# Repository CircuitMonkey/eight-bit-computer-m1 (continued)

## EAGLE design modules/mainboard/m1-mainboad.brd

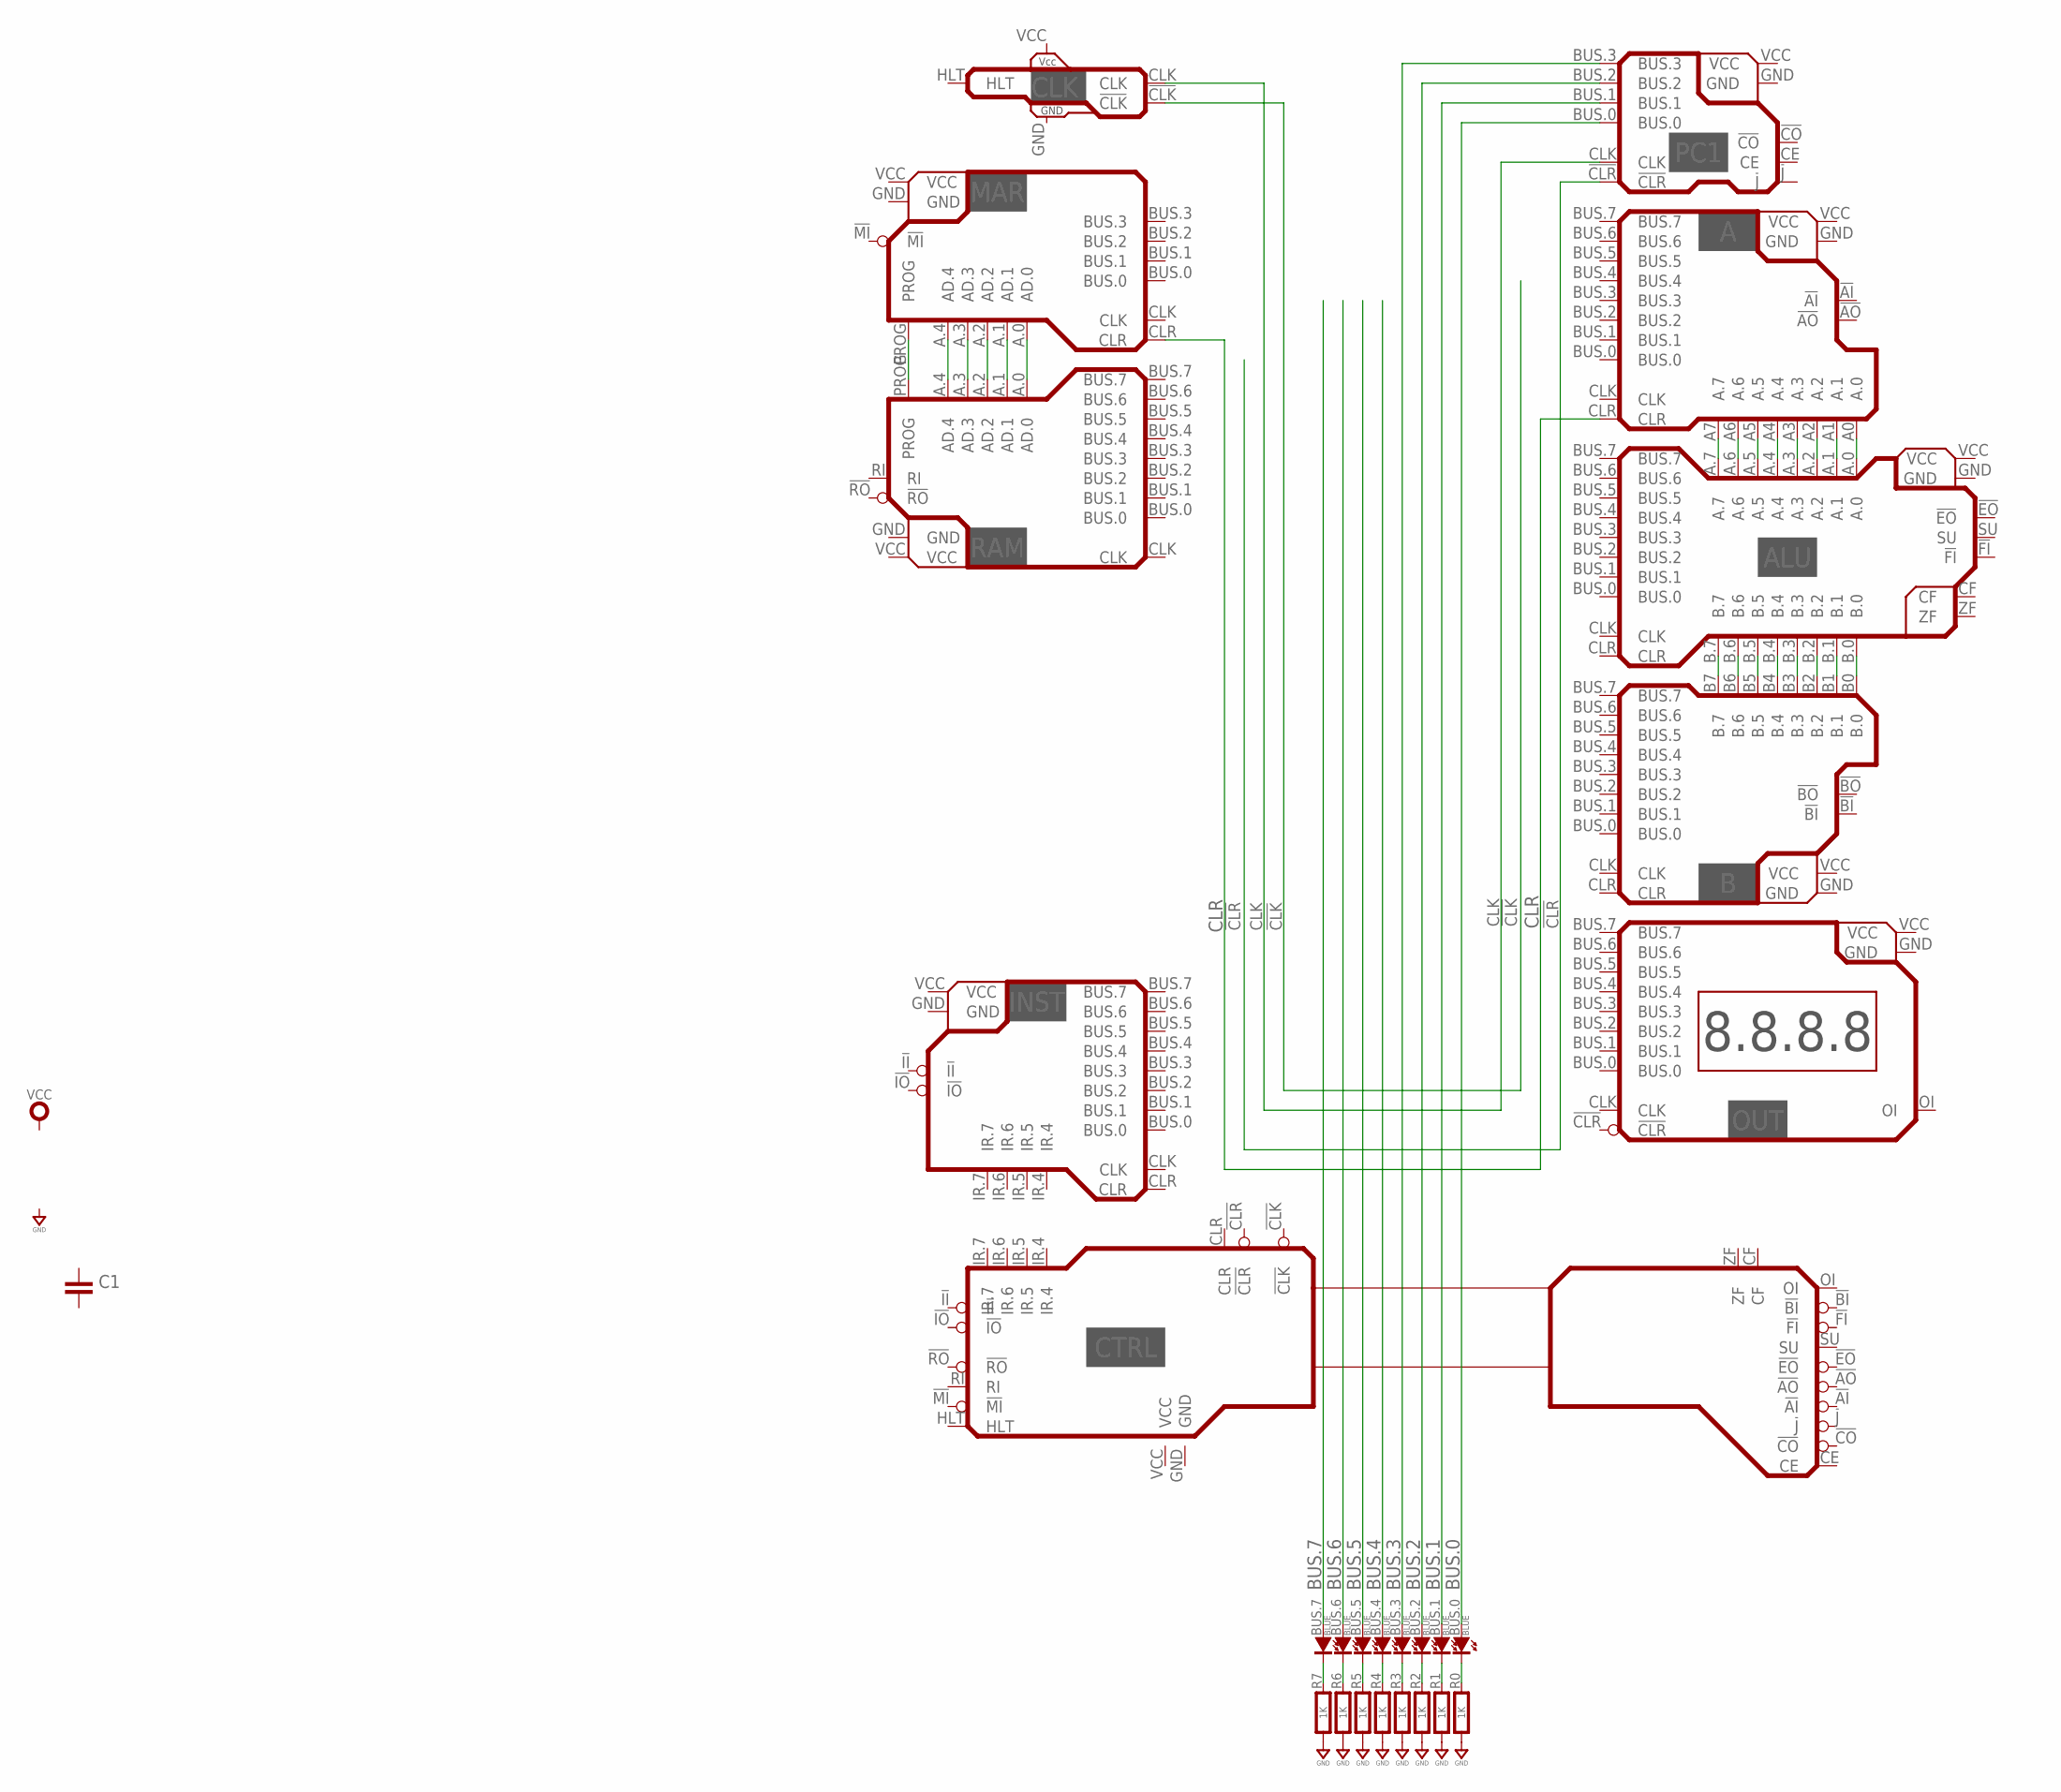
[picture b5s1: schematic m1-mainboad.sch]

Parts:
A: M1-REG-A-REV-A; M1-REG-A
ALU: M1-ALU-REV-A; M1-ALU
B: M1-REG-B-REV-A; M1-REG-B
BUS.0, BUS.1, BUS.2, BUS.3, BUS.4, BUS.5, BUS.6, BUS.7: BLUE; SMD_0603
C1: CAPACITOR0603; 0603-CAP
CLK: M1-CLOCKREV-A; M1-CLOCK
CTRL: M1-CONTROL-REV-A; M1-CONTROL
INST: M1-REG-INSTR-REV-A; M1-REG-I
MAR: M1-MAR-REV-A; M1-MAR
OUT: M1-REG-OUTPUT-REV-A; M1-REG-OUTPUT
PC1: M1-PROG-COUNTERREV-A; M1-PROGRAM-COUNTER
R0, R1, R2, R3, R4, R5, R6, R7: 1K; 0603-RES
RAM: M1-RAM-REV-A; M1-RAM

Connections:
!CLK: CLK.!CLK
!CLR: PC1.!CLR
BUS.0: BUS.0.A, PC1.BUS.0
BUS.1: BUS.1.A, PC1.BUS.1
BUS.2: BUS.2.A, PC1.BUS.2
BUS.3: BUS.3.A, PC1.BUS.3
BUS.4: BUS.4.A
BUS.5: BUS.5.A
BUS.6: BUS.6.A
BUS.7: BUS.7.A
CLK: CLK.CLK, PC1.CLK
CLR: A.CLR, MAR.CLR
GND: A.GND, ALU.GND, B.GND, CLK.GND, CTRL.GND, INST.GND, MAR.GND, OUT.GND, PC1.GND, R0.1, R1.1, R2.1, R3.1, R4.1, R5.1, R6.1, R7.1, RAM.GND
unnamed: BUS.0.K (C), R0.2
unnamed: BUS.1.K (C), R1.2
unnamed: BUS.2.K (C), R2.2
unnamed: BUS.3.K (C), R3.2
unnamed: BUS.4.K (C), R4.2
unnamed: BUS.5.K (C), R5.2
unnamed: BUS.6.K (C), R6.2
unnamed: BUS.7.K (C), R7.2
unnamed: A.A4 (A.4), ALU.A.4
unnamed: A.A5 (A.5), ALU.A.5
unnamed: A.A6 (A.6), ALU.A.6
unnamed: A.A7 (A.7), ALU.A.7
unnamed: A.A3 (A.3), ALU.A.3
unnamed: A.A2 (A.2), ALU.A.2
unnamed: A.A1 (A.1), ALU.A.1
unnamed: A.A0 (A.0), ALU.A.0
unnamed: ALU.B.4, B.B4 (B.4)
unnamed: ALU.B.5, B.B5 (B.5)
unnamed: ALU.B.6, B.B6 (B.6)
unnamed: ALU.B.7, B.B7 (B.7)
unnamed: ALU.B.3, B.B3 (B.3)
unnamed: ALU.B.2, B.B2 (B.2)
unnamed: ALU.B.1, B.B1 (B.1)
unnamed: ALU.B.0, B.B0 (B.0)
unnamed: MAR.A.0 (AD.0), RAM.A.0 (AD.0)
unnamed: MAR.A.1 (AD.1), RAM.A.1 (AD.1)
unnamed: MAR.A.2 (AD.2), RAM.A.2 (AD.2)
unnamed: MAR.A.3 (AD.3), RAM.A.3 (AD.3)
unnamed: MAR.A.4 (AD.4), RAM.A.4 (AD.4)
unnamed: MAR.PROG, RAM.PROG
VCC: A.VCC, ALU.VCC, B.VCC, CLK.VCC, CTRL.VCC, INST.VCC, MAR.VCC, OUT.VCC, PC1.VCC, RAM.VCC

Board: 2 copper layers, 27 parts (0 on the bottom side), 38 nets, no tracks yet.

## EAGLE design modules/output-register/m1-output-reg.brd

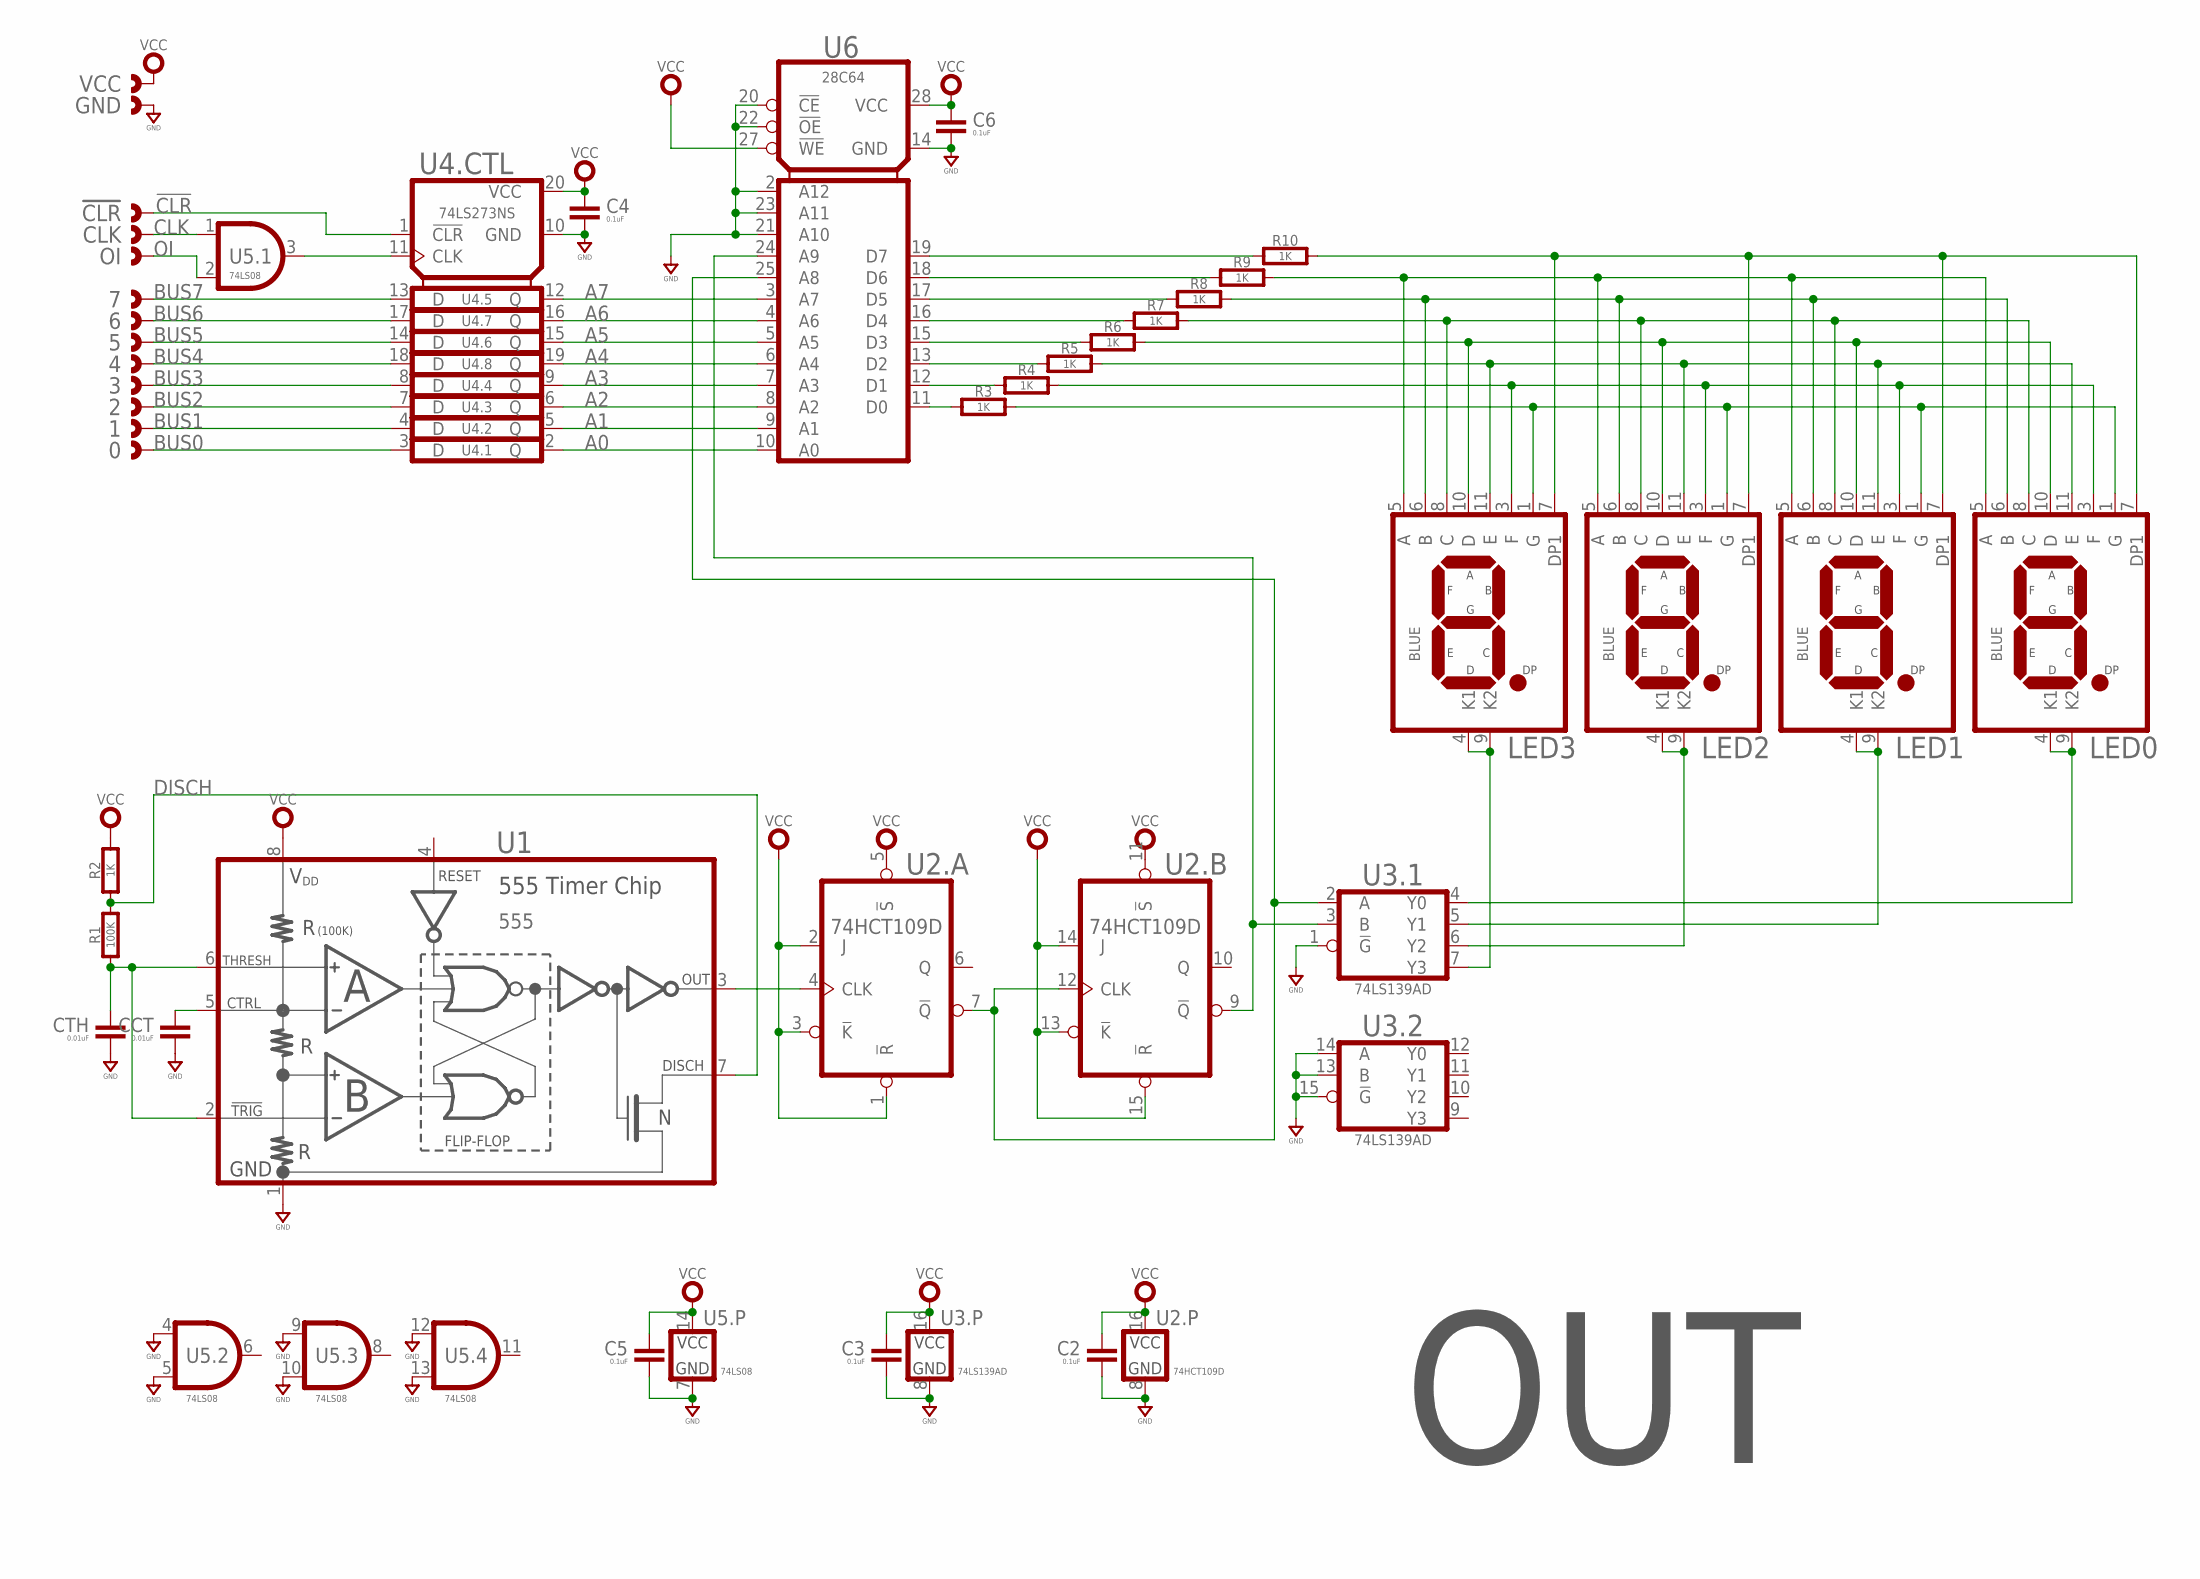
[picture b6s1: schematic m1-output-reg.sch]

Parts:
0, 1, 2, 3, 4, 5, 6, 7: CAST-01X1; CAST01-2.54MM
!CLR: CAST-01X1; CAST01-2.54MM
C2, C3, C4, C5, C6: 0.1uF; 0603-CAP
CCT: 0.01uF; 0603-CAP
CLK: CAST-01X1; CAST01-2.54MM
CTH: 0.01uF; 0603-CAP
GND: CAST-01X1; CAST01-2.54MM
LED0, LED1, LED2, LED3: BLUE; AVAGO-HDSM-281B-7SEG
OI: CAST-01X1; CAST01-2.54MM
R1: 100K; 0603-RES
R2, R3, R4, R5, R6, R7, R8, R9, R10: 1K; 0603-RES
U1: 555; SOP08
U2: 74HCT109D; SO16
U3: 74LS139AD; SO16
U4: 74LS273NS; SO20
U5: 74LS08; SOP14
U6: 28C64; SO28
VCC: CAST-01X1; CAST01-2.54MM

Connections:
!CLR: !CLR.1, U4.1 (!CLR)
A0: U4.2 (Q), U6.10 (A0)
A1: U4.5 (Q), U6.9 (A1)
A2: U4.6 (Q), U6.8 (A2)
A3: U4.9 (Q), U6.7 (A3)
A4: U4.19 (Q), U6.6 (A4)
A5: U4.15 (Q), U6.5 (A5)
A6: U4.16 (Q), U6.4 (A6)
A7: U4.12 (Q), U6.3 (A7)
BUS0: 0.1, U4.3 (D)
BUS1: 1.1, U4.4 (D)
BUS2: 2.1, U4.7 (D)
BUS3: 3.1, U4.8 (D)
BUS4: 4.1, U4.18 (D)
BUS5: 5.1, U4.14 (D)
BUS6: 6.1, U4.17 (D)
BUS7: 7.1, U4.13 (D)
CLK: CLK.1, U5.1 (A)
DISCH: R1.1, R2.1, U1.7 (DISCHARGE)
GND: C2.2, C3.2, C4.2, C5.2, C6.2, CCT.2, CTH.2, GND.1, U1.1 (GND), U2.8 (GND), U3.1 (!G), U3.8 (GND), U3.13 (B), U3.14 (A), U3.15 (!G), U4.10 (GND), U5.4 (A), U5.5 (B), U5.7 (GND), U5.9 (A), U5.10 (B), U5.12 (A), U5.13 (B), U6.2 (A12), U6.14 (GND), U6.20 (!CE), U6.21 (A10), U6.22 (!OE), U6.23 (A11)
unnamed: CTH.1, R1.2, U1.2 (TRIGGER#), U1.6 (THRESHOLD)
unnamed: CCT.1, U1.5 (CONTROL)
unnamed: U1.3 (OUTPUT), U2.4 (CLK)
unnamed: U2.9 (!Q), U3.3 (B), U6.24 (A9)
unnamed: U2.7 (!Q), U2.12 (CLK), U3.2 (A), U6.25 (A8)
unnamed: U4.11 (CLK), U5.3 (Y)
unnamed: R3.1, U6.11 (D0)
unnamed: R4.1, U6.12 (D1)
unnamed: R5.1, U6.13 (D2)
unnamed: R6.1, U6.15 (D3)
unnamed: R7.1, U6.16 (D4)
unnamed: R8.1, U6.17 (D5)
unnamed: R9.1, U6.18 (D6)
unnamed: R10.1, U6.19 (D7)
unnamed: LED0.7 (DP1), LED1.7 (DP1), LED2.7 (DP1), LED3.7 (DP1), R10.2
unnamed: LED0.5 (A), LED1.5 (A), LED2.5 (A), LED3.5 (A), R9.2
unnamed: LED0.6 (B), LED1.6 (B), LED2.6 (B), LED3.6 (B), R8.2
unnamed: LED0.4 (K1), LED0.9 (K2), U3.4 (Y0)
unnamed: LED0.8 (C), LED1.8 (C), LED2.8 (C), LED3.8 (C), R7.2
unnamed: LED0.10 (D), LED1.10 (D), LED2.10 (D), LED3.10 (D), R6.2
unnamed: LED0.11 (E), LED1.11 (E), LED2.11 (E), LED3.11 (E), R5.2
unnamed: LED0.3 (F), LED1.3 (F), LED2.3 (F), LED3.3 (F), R4.2
unnamed: LED0.1 (G), LED1.1 (G), LED2.1 (G), LED3.1 (G), R3.2
unnamed: LED3.4 (K1), LED3.9 (K2), U3.7 (Y3)
unnamed: LED2.4 (K1), LED2.9 (K2), U3.6 (Y2)
unnamed: LED1.4 (K1), LED1.9 (K2), U3.5 (Y1)
OI: OI.1, U5.2 (B)
VCC: C2.1, C3.1, C4.1, C5.1, C6.1, R2.2, U1.8 (VDD), U2.1 (!R), U2.2 (J), U2.3 (!K), U2.5 (!S), U2.11 (!S), U2.13 (!K), U2.14 (J), U2.15 (!R), U2.16 (VCC), U3.16 (VCC), U4.20 (VCC), U5.14 (VCC), U6.27 (!WE), U6.28 (VCC), VCC.1

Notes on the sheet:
OUT

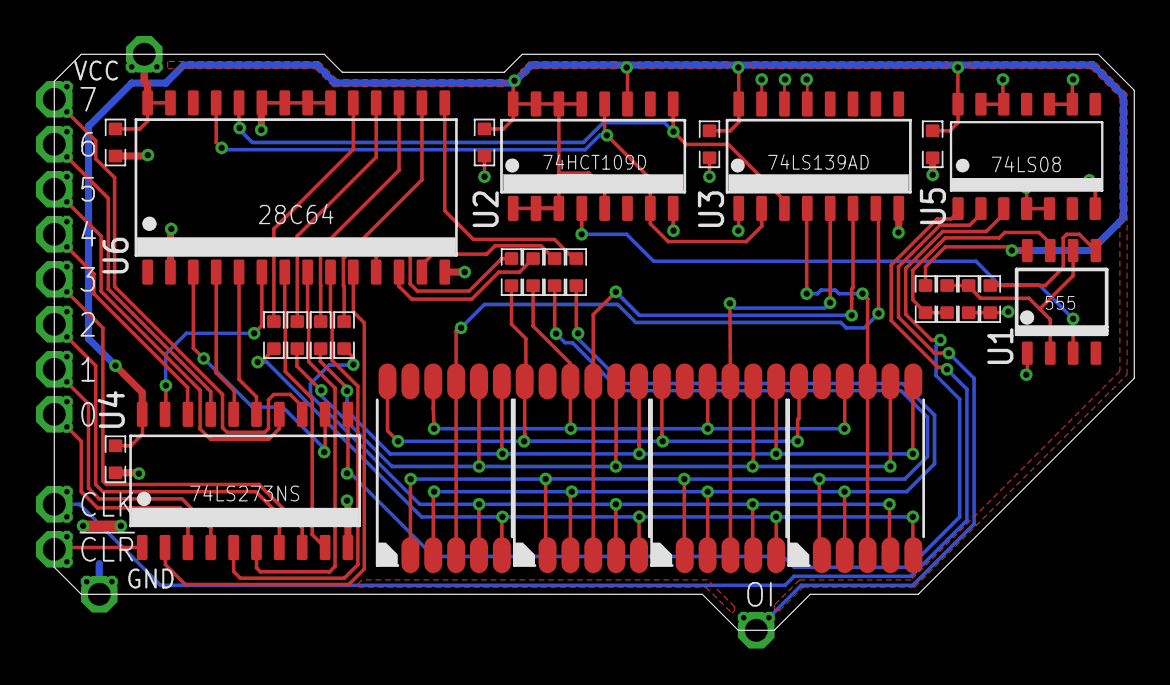
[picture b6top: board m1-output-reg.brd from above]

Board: 2 copper layers, 60.0 x 32.0 mm, 40 parts (0 on the bottom side), 48 nets.

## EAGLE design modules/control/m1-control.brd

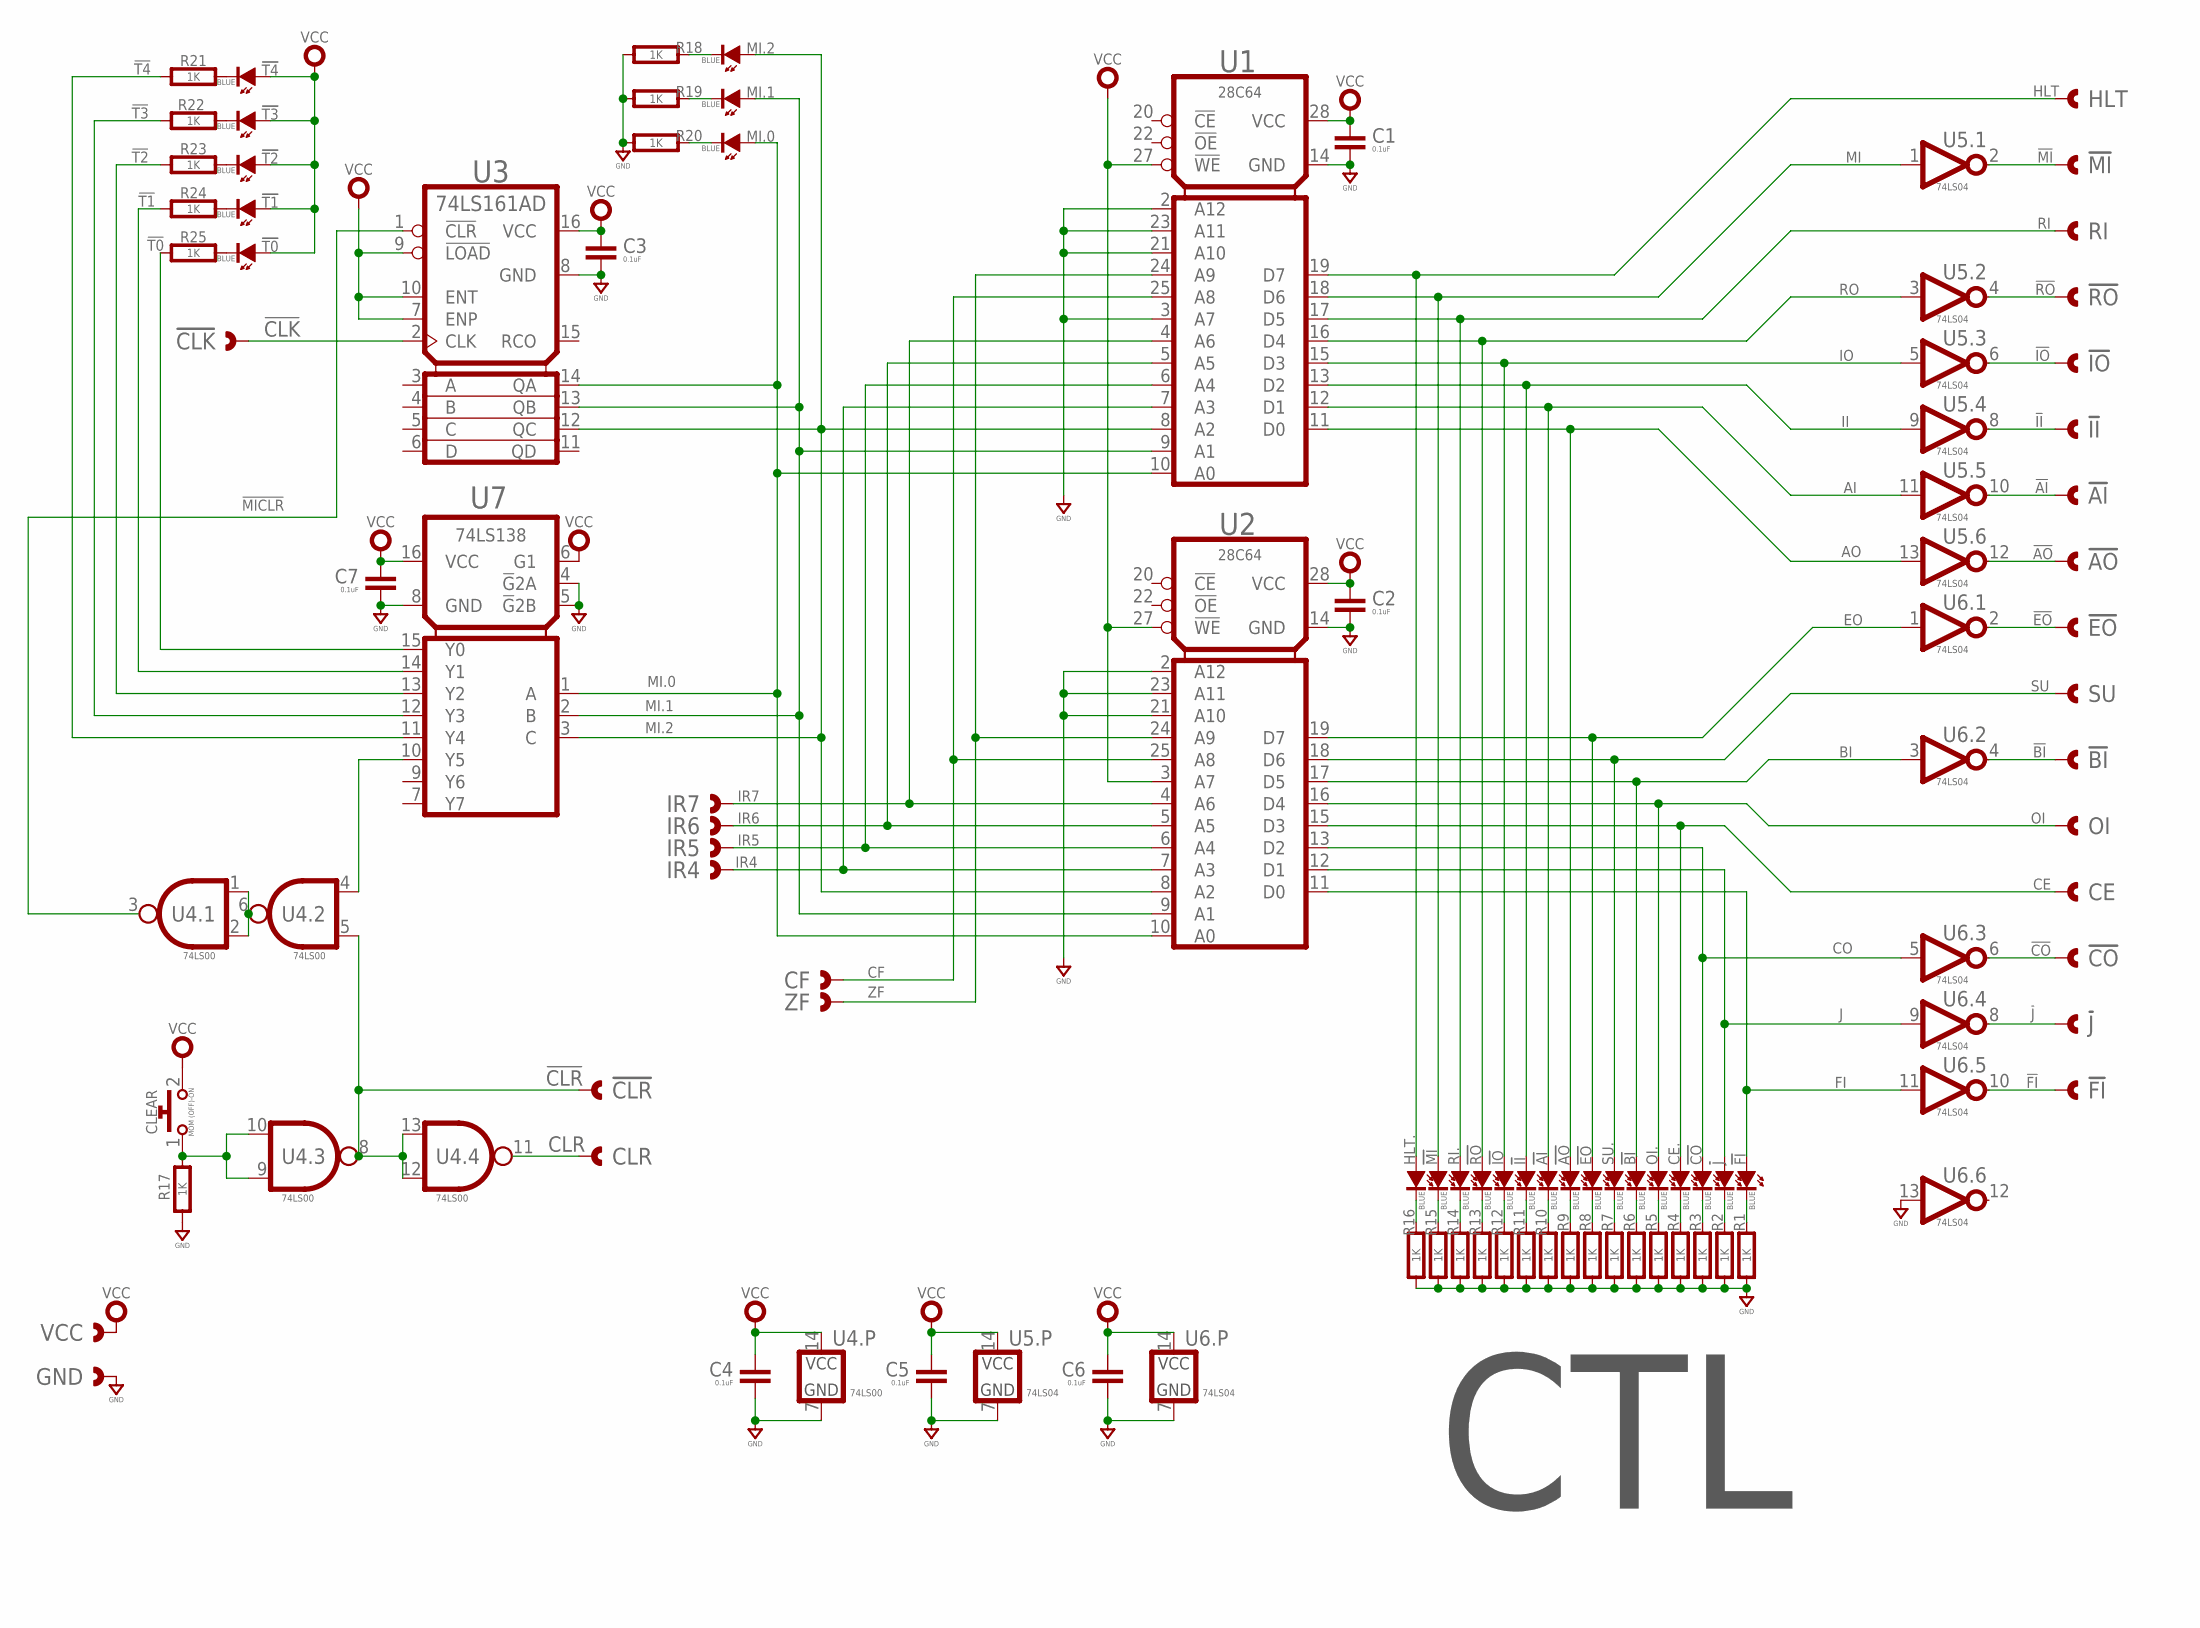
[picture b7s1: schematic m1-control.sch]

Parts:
!AI: CAST-01X1; CAST01-2.54MM
!AI!: BLUE; SMD_0603
!AO: CAST-01X1; CAST01-2.54MM
!AO!: BLUE; SMD_0603
!BI: CAST-01X1; CAST01-2.54MM
!BI!: BLUE; SMD_0603
!CLK: CAST-01X1; CAST01-2.54MM
!CLR: CAST-01X1; CAST01-2.54MM
!CO: CAST-01X1; CAST01-2.54MM
!CO!: BLUE; SMD_0603
!EO: CAST-01X1; CAST01-2.54MM
!EO!: BLUE; SMD_0603
!FI: CAST-01X1; CAST01-2.54MM
!FI!: BLUE; SMD_0603
!II: CAST-01X1; CAST01-2.54MM
!II!: BLUE; SMD_0603
!IO: CAST-01X1; CAST01-2.54MM
!IO!: BLUE; SMD_0603
!J: CAST-01X1; CAST01-2.54MM
!J!: BLUE; SMD_0603
!MI: CAST-01X1; CAST01-2.54MM
!MI!: BLUE; SMD_0603
!RO: CAST-01X1; CAST01-2.54MM
!RO!: BLUE; SMD_0603
!T0, !T1, !T2, !T3, !T4: BLUE; SMD_0603
C1, C2, C3, C4, C5, C6, C7: 0.1uF; 0603-CAP
CE: CAST-01X1; CAST01-2.54MM
CE.: BLUE; SMD_0603
CF: CAST-01X1; CAST01-2.54MM
CLEAR: MOM (OFF)-ON; SWITCH-0635-2P-SMD
CLR: CAST-01X1; CAST01-2.54MM
GND: CAST-01X1; CAST01-2.54MM
HLT: CAST-01X1; CAST01-2.54MM
HLT.: BLUE; SMD_0603
IR4, IR5, IR6, IR7: CAST-01X1; CAST01-2.54MM
MI.0, MI.1, MI.2: BLUE; SMD_0603
OI: CAST-01X1; CAST01-2.54MM
OI.: BLUE; SMD_0603
R1, R2, R3, R4, R5, R6, R7, R8, R9, R10, R11, R12, R13, R14, R15, R16, R17, R18, R19, R20, R21, R22, R23, R24, R25: 1K; 0603-RES
RI: CAST-01X1; CAST01-2.54MM
RI.: BLUE; SMD_0603
SU: CAST-01X1; CAST01-2.54MM
SU.: BLUE; SMD_0603
U1, U2: 28C64; SO28
U3: 74LS161AD; SO16
U4: 74LS00; SOP14
U5, U6: 74LS04; SOP14
U7: 74LS138; SO16
VCC: CAST-01X1; CAST01-2.54MM
ZF: CAST-01X1; CAST01-2.54MM

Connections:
!AI: !AI.1, U5.10 (Y)
!AO: !AO.1, U5.12 (Y)
!BI: !BI.1, U6.4 (Y)
!CLK: !CLK.1, U3.2 (CLK)
!CLR: !CLR.1, U4.5 (B), U4.8 (Y), U4.12 (B), U4.13 (A)
!CO: !CO.1, U6.6 (Y)
!EO: !EO.1, U6.2 (Y)
!FI: !FI.1, U6.10 (Y)
!II: !II.1, U5.8 (Y)
!IO: !IO.1, U5.6 (Y)
!J: !J.1, U6.8 (Y)
!MI: !MI.1, U5.2 (Y)
!MICLR: U3.1 (!CLR), U4.3 (Y)
!RO: !RO.1, U5.4 (Y)
!T0: R25.1, U7.15 (Y0)
!T1: R24.1, U7.14 (Y1)
!T2: R23.1, U7.13 (Y2)
!T3: R22.1, U7.12 (Y3)
!T4: R21.1, U7.11 (Y4)
AI: !AI!.A, U1.12 (D1), U5.11 (A)
AO: !AO!.A, U1.11 (D0), U5.13 (A)
BI: !BI!.A, U2.17 (D5), U6.3 (A)
CE: CE.1, CE..A, U2.15 (D3)
CF: CF.1, U1.25 (A8), U2.25 (A8)
CLR: CLR.1, U4.11 (Y)
CO: !CO!.A, U2.13 (D2), U6.5 (A)
EO: !EO!.A, U2.19 (D7), U6.1 (A)
FI: !FI!.A, U2.11 (D0), U6.11 (A)
GND: C1.2, C2.2, C3.2, C4.2, C5.2, C6.2, C7.2, GND.1, R1.1, R2.1, R3.1, R4.1, R5.1, R6.1, R7.1, R8.1, R9.1, R10.1, R11.1, R12.1, R13.1, R14.1, R15.1, R16.1, R17.1, R18.1, R19.1, R20.1, U1.2 (A12), U1.3 (A7), U1.14 (GND), U1.21 (A10), U1.23 (A11), U2.2 (A12), U2.14 (GND), U2.21 (A10), U2.23 (A11), U3.8 (GND), U4.7 (GND), U5.7 (GND), U6.7 (GND), U6.13 (A), U7.4 (!G!2A), U7.5 (!G!2B), U7.8 (GND)
HLT: HLT.1, HLT..A, U1.19 (D7)
II: !II!.A, U1.13 (D2), U5.9 (A)
IO: !IO!.A, U1.15 (D3), U5.5 (A)
IR4: IR4.1, U1.7 (A3), U2.7 (A3)
IR5: IR5.1, U1.6 (A4), U2.6 (A4)
IR6: IR6.1, U1.5 (A5), U2.5 (A5)
IR7: IR7.1, U1.4 (A6), U2.4 (A6)
J: !J!.A, U2.12 (D1), U6.9 (A)
MI: !MI!.A, U1.18 (D6), U5.1 (A)
MI.0: MI.0.A, U1.10 (A0), U2.10 (A0), U3.14 (QA), U7.1 (A)
MI.1: MI.1.A, U1.9 (A1), U2.9 (A1), U3.13 (QB), U7.2 (B)
MI.2: MI.2.A, U1.8 (A2), U2.8 (A2), U3.12 (QC), U7.3 (C)
unnamed: !FI!.K (C), R1.2
unnamed: !J!.K (C), R2.2
unnamed: !CO!.K (C), R3.2
unnamed: CE..K (C), R4.2
unnamed: OI..K (C), R5.2
unnamed: !BI!.K (C), R6.2
unnamed: R7.2, SU..K (C)
unnamed: !EO!.K (C), R8.2
unnamed: !AO!.K (C), R9.2
unnamed: !AI!.K (C), R10.2
unnamed: !II!.K (C), R11.2
unnamed: !IO!.K (C), R12.2
unnamed: !RO!.K (C), R13.2
unnamed: R14.2, RI..K (C)
unnamed: !MI!.K (C), R15.2
unnamed: HLT..K (C), R16.2
unnamed: U4.1 (A), U4.2 (B), U4.6 (Y)
unnamed: U4.4 (A), U7.10 (Y5)
unnamed: MI.2.K (C), R18.2
unnamed: CLEAR.1, R17.2, U4.9 (B), U4.10 (A)
unnamed: MI.1.K (C), R19.2
unnamed: MI.0.K (C), R20.2
unnamed: !T4.K (C), R21.2
unnamed: !T3.K (C), R22.2
unnamed: !T2.K (C), R23.2
unnamed: !T1.K (C), R24.2
unnamed: !T0.K (C), R25.2
OI: OI.1, OI..A, U2.16 (D4)
RI: RI.1, RI..A, U1.17 (D5)
RO: !RO!.A, U1.16 (D4), U5.3 (A)
SU: SU.1, SU..A, U2.18 (D6)
VCC: !T0.A, !T1.A, !T2.A, !T3.A, !T4.A, C1.1, C2.1, C3.1, C4.1, C5.1, C6.1, C7.1, CLEAR.2, U1.27 (!WE), U1.28 (VCC), U2.3 (A7), U2.27 (!WE), U2.28 (VCC), U3.7 (ENP), U3.9 (!LOAD), U3.10 (ENT), U3.16 (VCC), U4.14 (VCC), U5.14 (VCC), U6.14 (VCC), U7.6 (G1), U7.16 (VCC), VCC.1
ZF: U1.24 (A9), U2.24 (A9), ZF.1

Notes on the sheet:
CTL

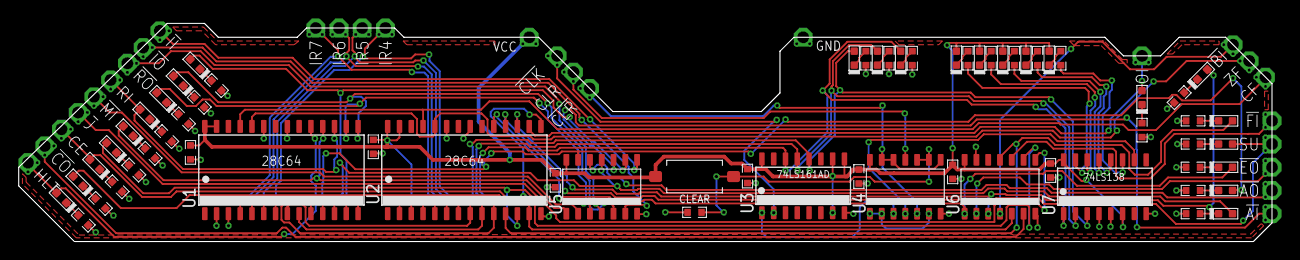
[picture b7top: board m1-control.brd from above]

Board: 2 copper layers, 135.0 x 23.5 mm, 91 parts (0 on the bottom side), 74 nets.
